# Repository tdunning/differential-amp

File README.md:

# Differential Amplifer

This circuit is designed to be a single supply differential amplifier module which can be used in building Manhattan style prototypes.

Use whatever op-amp has a compatible pinout (there are dozens) and pick your gain. All of the passives are laid out as 0805 components to make soldering easier.

Enjoy!

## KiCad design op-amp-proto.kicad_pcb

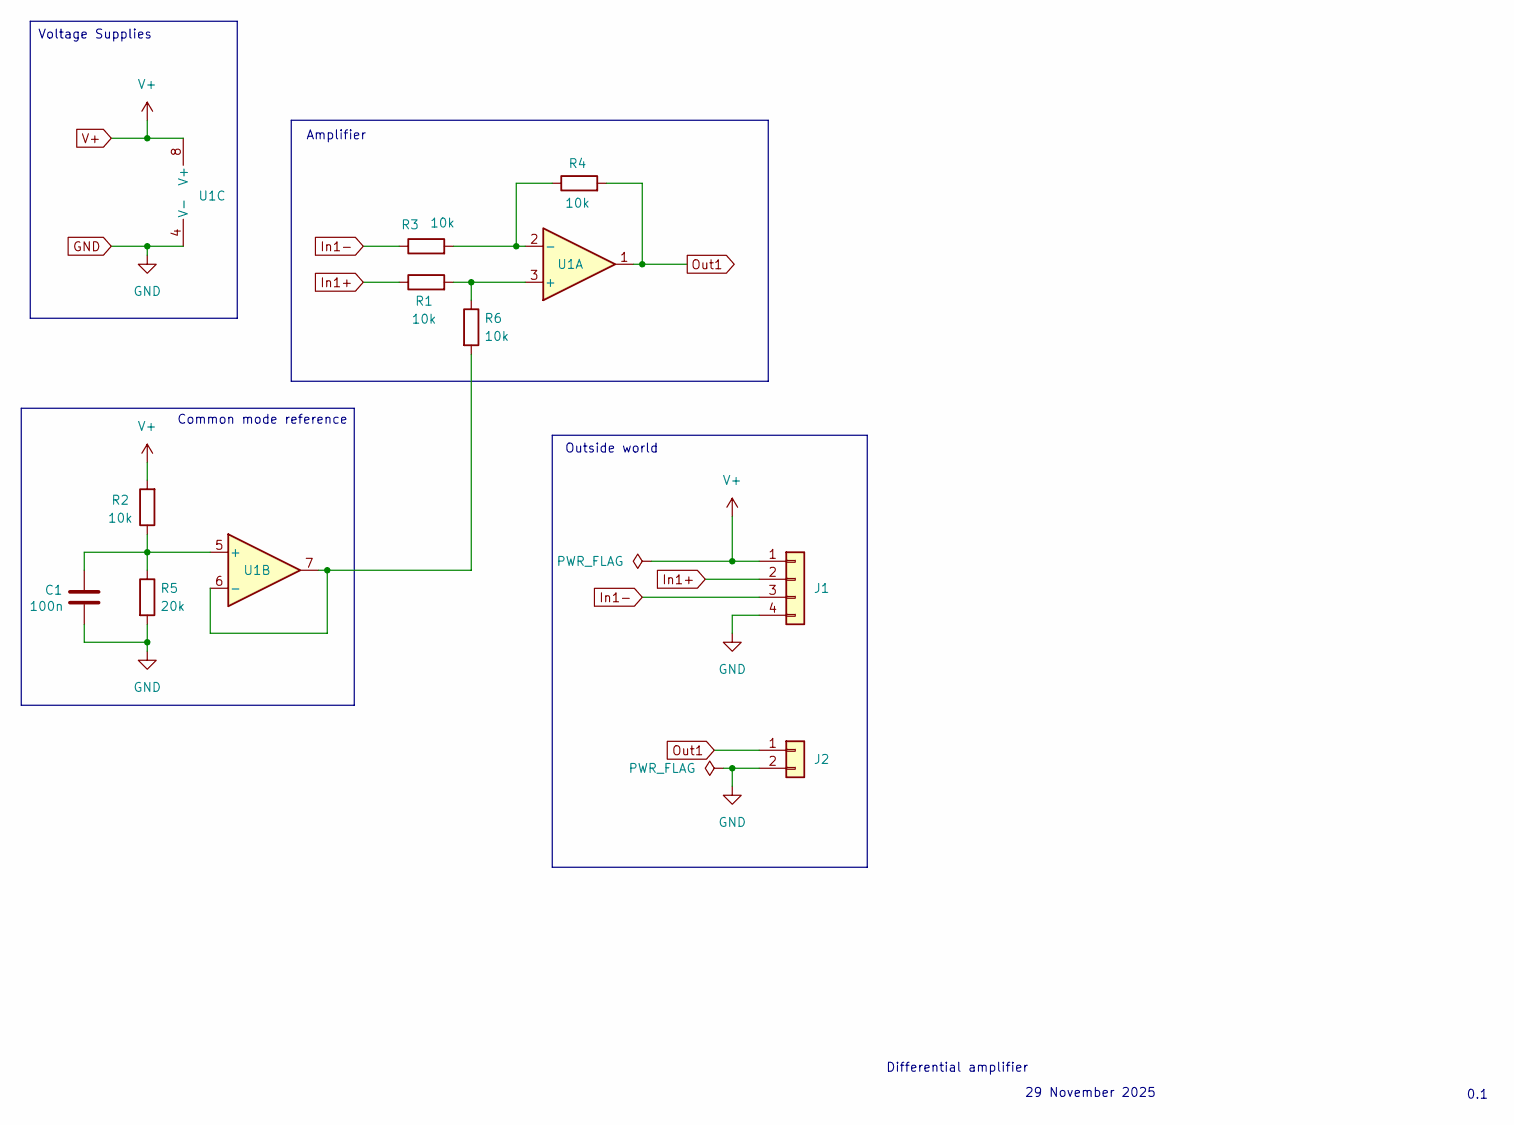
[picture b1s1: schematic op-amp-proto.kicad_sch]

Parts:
C1: 100n; C_0805_2012Metric_Pad1.18x1.45mm_HandSolder
J1: Conn_01x012_MountingPin; PinHeader_1x04_P2.54mm_Vertical
J2: Conn_01x012_MountingPin; PinHeader_1x02_P2.54mm_Vertical
R1, R2, R3, R4, R6: 10k; R_0805_2012Metric_Pad1.20x1.40mm_HandSolder
R5: 20k; R_0805_2012Metric_Pad1.20x1.40mm_HandSolder
U1: Opamp_Dual; SOIC-8_3.9x4.9mm_P1.27mm

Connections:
GND: C1.1, J1.4, J2.2, R5.2, U1.4 (V-)
In1+: J1.2, R1.1
In1-: J1.3, R3.1
unnamed: R1.2, R6.1, U1.3 (+)
unnamed: R3.2, R4.1, U1.2 (-)
unnamed: C1.2, R2.1, R5.1, U1.5 (+)
unnamed: R6.2, U1.6 (-), U1.7
Out1: J2.1, R4.2, U1.1
V+: J1.1, R2.2, U1.8 (V+)

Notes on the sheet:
Voltage Supplies
0.1
Outside world
29 November 2025
Differential amplifier
Amplifier
Common mode reference

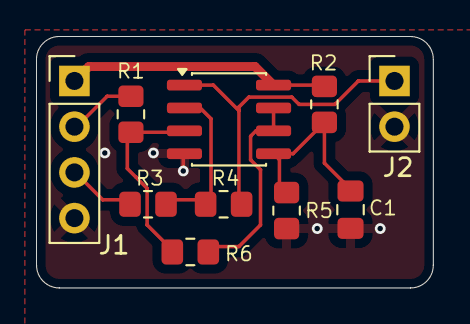
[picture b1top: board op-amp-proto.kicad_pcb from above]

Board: 2 copper layers, 22.0 x 14.0 mm, 10 parts (0 on the bottom side), 9 nets.

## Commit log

2025-12-14 Added README
